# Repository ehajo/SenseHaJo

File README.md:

# SenseHaJo
Alle Infos über das SenseHaJo Projekt.

Die Youtube-Livestream Playlist befindet sich hier: <a href="https://www.youtube.com/playlist?list=PLOau4iU1BNa8n_ICx9ISsTIcdp01ndQ__">Playlist on Youtube</a>

Livestreams immer hier auf Twitch: <a href="https://www.twitch.tv/ehajo">Link zu Twitch</a>

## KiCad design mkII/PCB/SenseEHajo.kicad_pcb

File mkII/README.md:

# SenseHaJo

Mark II ist die aktuellste Version des SenseHaJo-Projekts. Mathias aka Calm aka "der andere" hat in KiCAD ein komplettes Projekt hochgezogen.

Ich programmiere die Software mit ESPHome und mit Hilfe von ChatGPT.

Die Platine besitzt nun einen leistungsstarken ESP32 Prozessor.

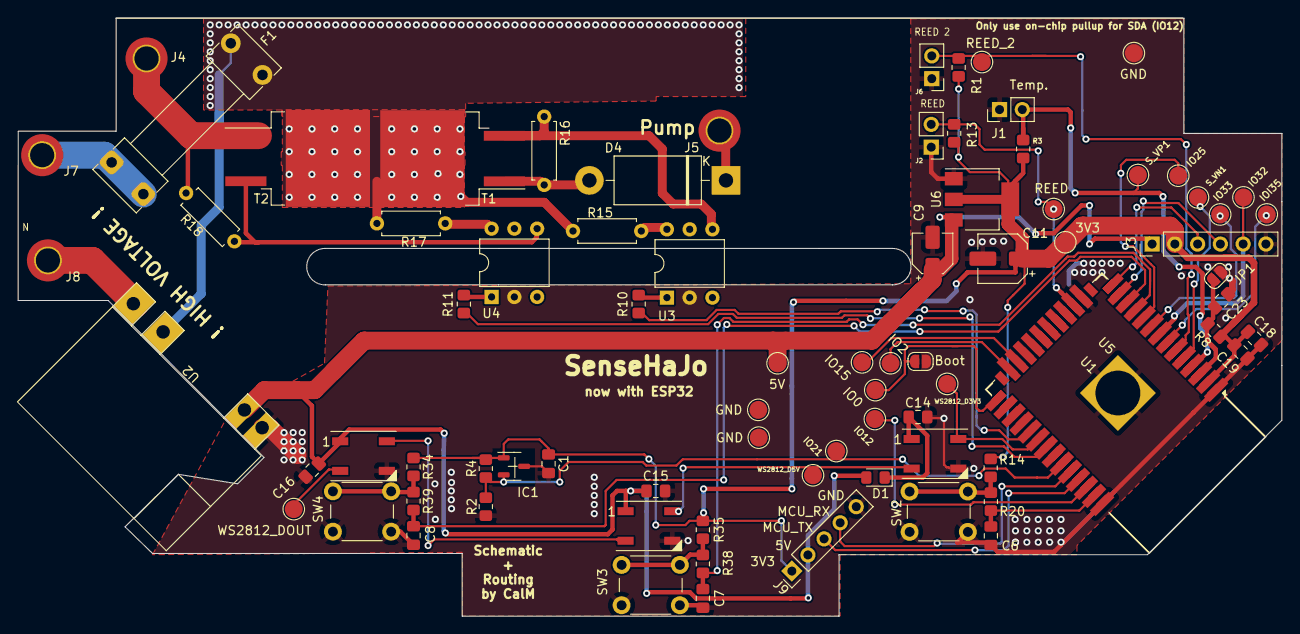
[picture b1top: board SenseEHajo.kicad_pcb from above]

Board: 2 copper layers, 141.0 x 66.7 mm, 80 parts (0 on the bottom side), 47 nets.

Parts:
3V3: 3V3; TestPoint_Pad_D2.0mm
5V: 5V; TestPoint_Pad_D2.0mm
C1, C6, C7, C8, C14, C15, C16, C19: 100nF / 10V; C_0805_2012Metric_Pad1.18x1.45mm_HandSolder
C9: 10uF/10V; CP_Elec_4x4.5
C11: 47uF/10V; CP_Elec_5x5.3
C18, C23: 10uF / 10V; C_0805_2012Metric_Pad1.18x1.45mm_HandSolder
D1: 1N4006; D_0805_2012Metric_Pad1.15x1.40mm_HandSolder
D3, D6, D7: WS2812B; WS2812B_SMD_HandSolder
D4: 1N4006; D_DO-201AD_P15.24mm_Horizontal
F1: 0.5A / 230VAC; Fuseholder_Clip-5x20mm_Littelfuse_111_Lateral_P18.80x5.00mm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
GND: 5V; TestPoint_Pad_D2.0mm
GND#2, GND#3: 5V; TestPoint_Pad_D2.0mm
IC1: SL353LT; SOT-23-3
IO0, IO2, IO15, IO21, IO25, IO32, IO33: IO32; TestPoint_Pad_D2.0mm
IO12: I2C_DISP_SDA_3V3; TestPoint_Pad_D2.0mm
IOI35: IO32; TestPoint_Pad_D2.0mm
J1: Conn_01x02_Male; PinHeader_1x02_P2.54mm_Vertical
J2, J6: REED; PinHeader_1x02_P2.54mm_Vertical
J3: RTC ( DS3231); PinHeader_1x06_P2.54mm_Vertical
J4: Heizung L; MountingHole_2.7mm_M2.5_DIN965_Pad_TopBottom
J5: Pumpe L; MountingHole_2.7mm_M2.5_DIN965_Pad_TopBottom
J7: L; MountingHole_2.7mm_M2.5_DIN965_Pad_TopBottom
J8: N; MountingHole_2.7mm_M2.5_DIN965_Pad_TopBottom
J9: Prog; PinHeader_1x05_P2.54mm_Vertical
JP1: Jumper_2_Open; SolderJumper-2_P1.3mm_Open_RoundedPad1.0x1.5mm
JP2: Boot; SolderJumper-2_P1.3mm_Open_RoundedPad1.0x1.5mm
R1, R2, R4, R8, R13, R14, R34, R35: 10k; R_0805_2012Metric_Pad1.20x1.40mm_HandSolder
R3: 3k3/1%; R_0805_2012Metric_Pad1.20x1.40mm_HandSolder
R10, R11: 150R; R_0805_2012Metric_Pad1.20x1.40mm_HandSolder
R15, R17: 360R; R_Axial_DIN0207_L6.3mm_D2.5mm_P7.62mm_Horizontal
R16, R18: 330R; R_Axial_DIN0207_L6.3mm_D2.5mm_P7.62mm_Horizontal
R20, R38, R39: 1k; R_0805_2012Metric_Pad1.20x1.40mm_HandSolder
REED: IO32; TestPoint_Pad_D2.0mm
REED_2: IO32; TestPoint_Pad_D2.0mm
SW2: SW1 ( Boot ); SW_PUSH_6mm
SW3: MACHINE_SW2; SW_PUSH_6mm
SW4: MACHINE_SW3; SW_PUSH_6mm
S_VN1: IO32; TestPoint_Pad_D2.0mm
S_VP1: IO32; TestPoint_Pad_D2.0mm
T1, T2: QJ8025; TO-263-3_TabPin2
U1: ESP32-WROOM-32; ESP32-WROOM-32_HandSolder
U2: SKU011012
U3, U4: MOC3043M; DIP-6_W7.62mm
U5: ESP32-S3-WROOM-1
U6: LM1117-3.3; SOT-223-3_TabPin2
WS2812_D3V3, WS2812_D5V, WS2812_DOUT: TestPoint; TestPoint_Pad_D2.0mm

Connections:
+3V3: 3V3.1, C1.1, C11.1, C18.2, C19.2, IC1.1 (VCC), J3.2, J9.1, R1.1, R3.1, R4.1, R8.1, R13.1, R14.1, R34.1, R35.1, U1.2 (VDD), U6.2 (VO)
+5V: 5V.1, C9.1, C15.1, C16.1, D1.2 (A), D6.1 (VDD), D7.1 (VDD), J3.1, J9.2, U2.4 (5V), U6.3 (VI)
EN: C23.1, JP1.2 (B), R8.2, U1.3 (EN)
ESP32_ADC: J1.2, R3.2, S_VP1.1, U1.4 (SENSOR_VP)
GND: C1.2, C6.1, C7.1, C8.1, C9.2, C11.2, C14.2, C15.2, C16.2, C18.1, C19.1, C23.2, D3.3 (VSS), D6.3 (VSS), D7.3 (VSS), GND.1, IC1.3 (GND), J1.1, J2.1, J3.6, J6.1, J9.5, JP1.1 (A), JP2.2 (B), R2.2, SW2.2, SW3.2, SW4.2, U1.1 (GND), U1.15 (GND), U1.38 (GND), U1.39 (GND), U2.3 (GND), U3.2, U4.2, U6.1 (GND)
HAL_SENSOR: IC1.2 (OUTPUT), IO21.1, R2.1, R4.2, U1.33 (IO21)
Heizung_MOC: R11.2, U1.31 (IO19)
I2C_DSP_SCL: IO0.1, JP2.1 (A), U1.25 (IO0)
I2C_DSP_SDA: IO12.1, U1.36 (IO22)
IO32: IO32.1, J3.5, U1.8 (IO32)
LOAD_230V: F1.2, R15.2, R17.2, T1.2 (A2), T2.2 (A2), U2.2 (N)
L_230V: F1.1, J7.1
MCU_RX: J9.4, U1.34 (RXD0/IO3)
MCU_TX: J9.3, U1.35 (TXD0/IO1)
N_230V: J8.1, U2.1 (L)
unnamed: C14.1, D1.1 (K), D3.1 (VDD)
unnamed: D3.2 (DOUT), D6.4 (DIN), WS2812_D5V.1
unnamed: D4.2 (A), R16.2, T1.1 (A1)
unnamed: D4.1 (K), J5.1
unnamed: D6.2 (DOUT), D7.4 (DIN)
unnamed: D7.2 (DOUT), WS2812_DOUT.1
unnamed: J4.1, R18.2, T2.1 (A1)
unnamed: R10.1, U3.1
unnamed: R11.1, U4.1
unnamed: R14.2, R20.1, SW2.1
unnamed: R15.1, U3.6
unnamed: R17.1, U4.6
unnamed: R34.2, R39.1, SW4.1
unnamed: R35.2, R38.1, SW3.1
unnamed: R16.1, T1.3 (G), U3.4
unnamed: R18.1, T2.3 (G), U4.4
unnamed: IO2.1, U1.24 (IO2)
unnamed: IO15.1, U1.23 (IO15)
unnamed: C6.2, R20.2, U1.37 (IO23)
unnamed: IO25.1, U1.10 (IO25)
unnamed: C7.2, R38.2, U1.11 (IO26)
unnamed: C8.2, R39.2, U1.12 (IO27)
unnamed: IO33.1, U1.9 (IO33)
unnamed: IOI35.1, U1.7 (IO35)
unnamed: S_VN1.1, U1.5 (SENSOR_VN)
unnamed: U5.1 (GND), U5.40 (GND), U5.41 (GND)
PUMP_MOC: R10.2, U1.29 (IO5)
REED_IN: J2.2, R13.2, REED.1, U1.16 (IO13)
REED_IN_2: J6.2, R1.2, REED_2.1, U1.6 (IO34)
SCL_3V3: J3.4, U1.13 (IO14)
SDA_3V3: J3.3, U1.14 (IO12)
WS2812_3V3: D3.4 (DIN), U1.30 (IO18), WS2812_D3V3.1

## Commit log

2017-06-27 :lollipop: Added .gitattributes & .gitignore files
2023-06-17 Added Clean / Fill boiler
    Quick hack to add fill boilder
    Code untested
2023-08-19 Update fill boiler
    Bugfix
2023-08-19 update button driver
    Update
2023-09-12 Added GPIO command
2023-09-12 Bugfix for commands
    Resolves bug that prevents compiling
2023-09-12 Fix GET GPIO
    Shall fix GET GPIO X command
2023-09-12 Updates switch commands
    Should fix command GPIO
2023-09-16 Refactor of Commands in Command interpreter
    Refactored Commands in Command interprerter
    Also some minor bug fixes
2023-09-16 Added Function to abort cold clean
    Enables to abort cold clean function
2023-09-17 FSM will now enter IDLE after Boiler fill or cold clean
    FSM will now enter IDLE after Boiler fill or cold clean
2023-09-20 Delay in Startup go the stable IO
    Wait untill VCC is stable
2023-09-20 Debug session
    Some changes for power on on reset. not working yet.
2024-02-08 Alles Neu
    Neue Ordnerstruktur etc
2024-02-09 mkI upload
    Upload der PCB Daten von mkI
2024-04-17 Add submodules for ESP32 version
    Add submodules for ESP32 Version
2024-05-15 Initial Commit
    Streamfortschritt von esphome und unseren überlegungen zu der statemachine
2024-05-27 something final
    Funktioniert soweit, Kaffeekochen klappt, muss noch ein wenig optimiert werden. Stand Stream vom 22.05.: https://youtu.be/AHHM0ns9L-4
2024-06-03 initial commit
    added basic secrets.yaml file
2025-02-18 Moved files. Sorted etc.
2025-02-21 grokifiziert
    Einmal durch grok gejagt zum optimieren
2025-02-25 initial commit
    Rahmen für OLED-Display für Deckel, damit der Rand schön schwarz ist.
2025-02-25 Aktuelle Version Stream 24.02.
    Display wird nun korrekt angesteuert und zeigt Werte an
2025-02-28 massive update
    - heizungsregelung angepasst von grok auf scripting statt climate.
    - displayansteuerung implementiert und funktional
2025-03-04 initial commit
    - added courier bold font
    - added ehajo_bw.xbm ehajo-logo for bootscreen
2025-03-04 small changes
    added bootscreen
